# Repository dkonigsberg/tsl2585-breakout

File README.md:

# TSL2585 Breakout Board

This repository contains the [KiCad](http://kicad.org/) project
with the complete circuit schematics and PCB layout for a breakout
board that supports the [TSL2585](https://ams.com/en/tsl2585) light sensor from
[AMS](https://ams-osram.com/). This sensor has Photopic, UV-A, and IR channels,
as well as flicker detection.

AMS makes several other sensors that are extremely similar to this one, but they
are not pin compatible.

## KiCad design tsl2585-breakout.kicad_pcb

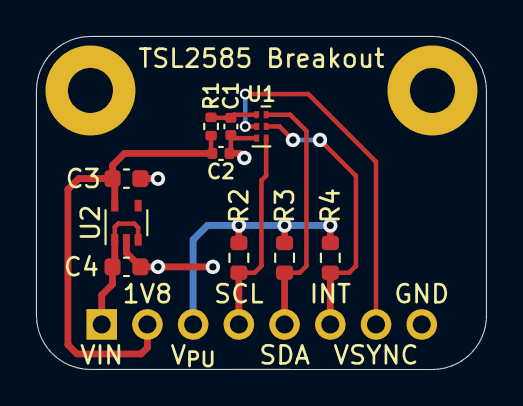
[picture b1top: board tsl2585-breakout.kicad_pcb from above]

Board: 2 copper layers, 25.0 x 18.5 mm, 13 parts (1 on the bottom side), 9 nets.

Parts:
C1: 1uF; C_0402_1005Metric
C2: 4.7uF; C_0402_1005Metric
C3, C4: 1uF; C_0603_1608Metric
H1, H2: MountingHole; MountingHole_2.5mm_Pad
J1: Conn_01x08; PinHeader_1x08_P2.54mm_Vertical
R1: 22R; R_0402_1005Metric
R2, R3, R4: 10K; R_0603_1608Metric
U1: TSL2585; AMS_TSL2585_OLGA-6_2x1mm_P0.65mm
U2: MIC5365-1.8YC5; SOT-353_SC-70-5

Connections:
+1V8: C2.1, C3.2, J1.2, R1.2, U2.5 (VOUT)
/SENSOR_INT: J1.6, R4.2, U1.5 (INT)
/SENSOR_SCL: J1.4, R2.2, U1.4 (SCL)
/SENSOR_SDA: J1.5, R3.2, U1.6 (SDA)
/SENSOR_VSYNC: J1.7, U1.2 (VSYNC/GPIO)
/V_{PU}: J1.3, R2.1, R3.1, R4.1
GND: C1.2, C2.2, C3.1, C4.1, J1.8, U1.3 (VSS), U2.2 (GND)
unnamed: C1.1, R1.1, U1.1 (VDD)
VCC: C4.2, J1.1, U2.1 (VIN), U2.3 (EN)

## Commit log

2023-11-27 Initial project repository setup
    Pulled in footprints and symbols from other projects using this same
    sensor.
    Configured schematic and layout page properties.
2023-11-27 Schematic for breakout board complete
2023-11-27 PCB layout done
2023-11-27 Breakout board ready for fab
2023-12-03 Add license file
2023-12-03 Add images to project
2023-12-03 Link fixup
2023-12-05 Update project to remove alternative sensors
    As it turns out, these other sensors are not pin compatible.
